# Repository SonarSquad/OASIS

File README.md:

# OASIS
Contains the complete code, circuit schematics and designs for the OASIS prototype system.
The full OASIS - A low-cost modular echosounder thesis report should also be red for a better understanding if further development of the system are to be investigated.  

**CONTENT: folder and content**
- LNA_Rev3: PCB design files for the LNA board (ALTIUM).
- Oasis_ADC_PCB: PCB design files and gerbers for the ADC board (KICAD).
- Oasis_MCU_bridge_PCB: PCB design files and gerbers for MCU board (KICAD).
- Python code and drivers: Main python script and C- code drivers for the OASIS system
- MCU_ATmega4809: Code for waveform-generation on the ATmega4809. 
- SPI_test_alternative_ADC: Example code for setting up SPI communication on the Raspberry Pi 4 (not used in OASIS prototype).  

**HARDWARE modules:**
- LNA board - Low noise amplifier. (designed and tested)
- MCU board - ATmega4809 Full-bridge module. (designed and tested)
- ADC board - ADS8422 board Analog to Digital converter. (designed and tested)
- Raspberry pi 4 model B (4GB RAM). (bought and tested)

**OASIS Prototype achievements:** 
1. System startup, Transmit a pulse at preset frequency (200kHz).
    - Pulse generaton is done on sepparate microcontroller (MCU).
    
2. Amplify returning echo with LNA.  
    
3. Sample returning echo, (switch not developed yet - two transducers used while testing, one for transmit and one for receive). 
    - Receive and sample incomming returning echo. Sampling @ 1.7 Msps.  

4. Plotting and light processing of received signal.
    - Plot: FFT. 
    - Plot: Time vs. voltage. 

________________________________________________________________________________________________________
**CONTACT:** 
- Martin Ericsson - tlf: 92649342, email: martincse94@gmail.com 
- Tor K. Gjerde - tlf: 46934462, email: torgjerde.nor@gmail.com
- Torbjørn Willson - tlf: 46810798, email: torbjorw@ntnu.no
- Einar Avdem - tlf: 98813120, email: einarav@stud.ntnu.no

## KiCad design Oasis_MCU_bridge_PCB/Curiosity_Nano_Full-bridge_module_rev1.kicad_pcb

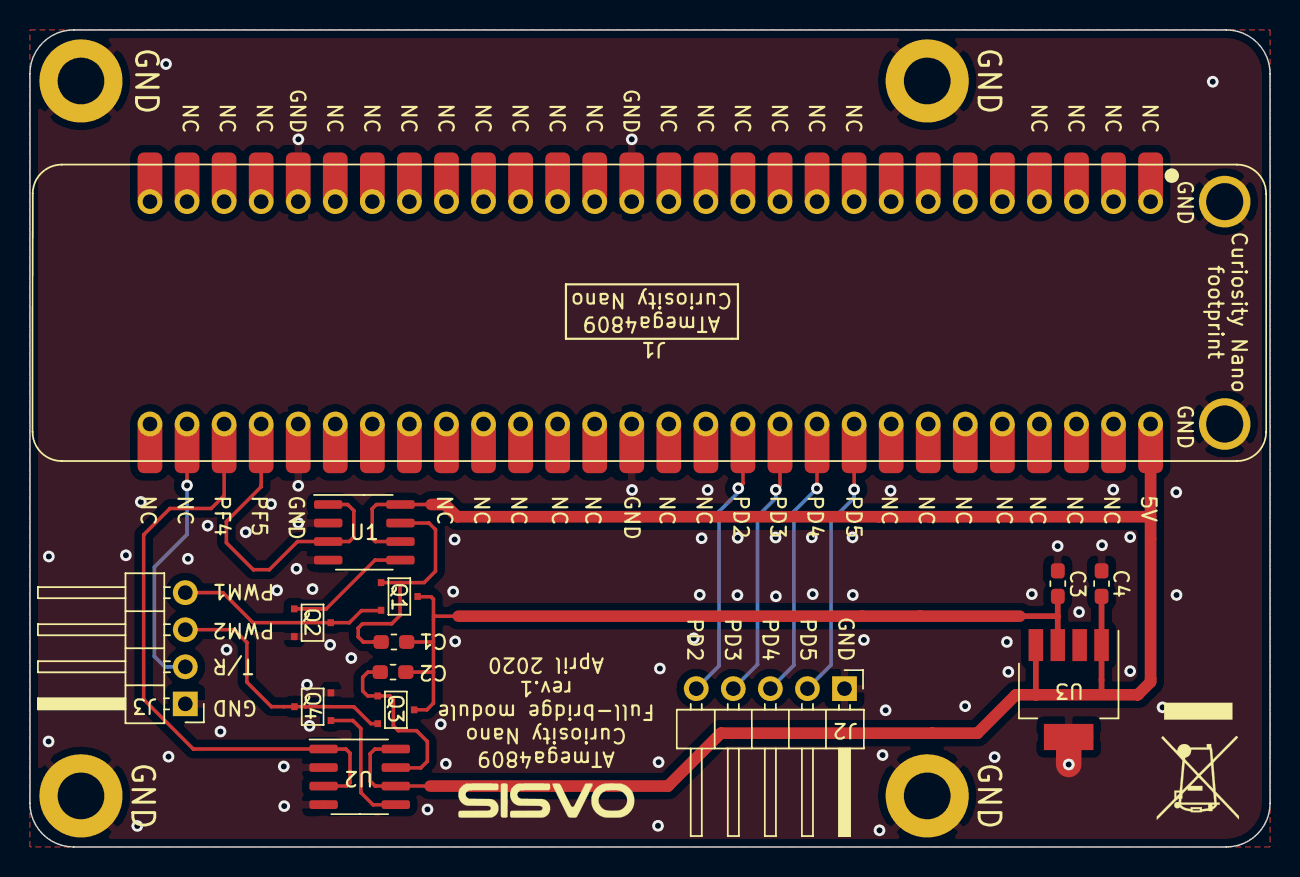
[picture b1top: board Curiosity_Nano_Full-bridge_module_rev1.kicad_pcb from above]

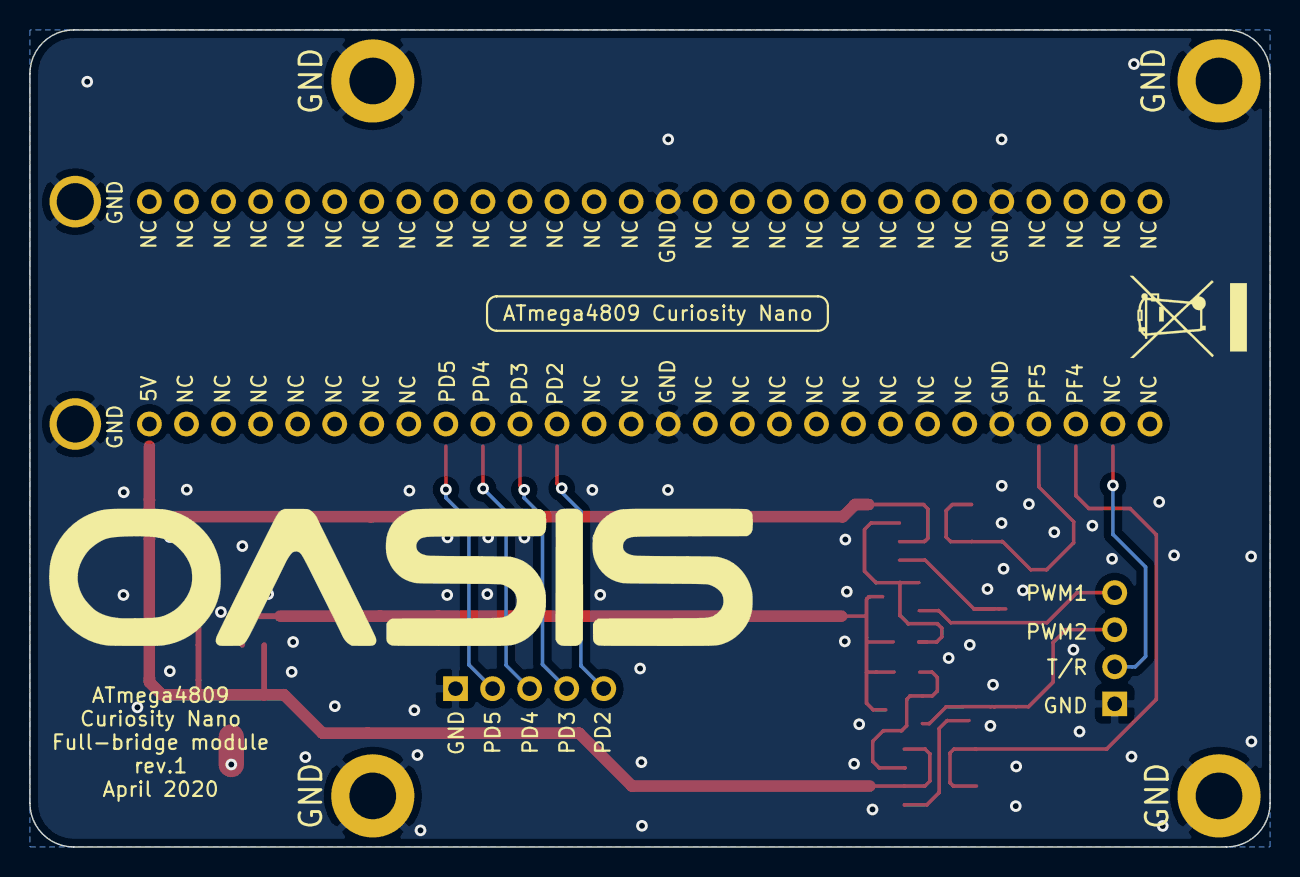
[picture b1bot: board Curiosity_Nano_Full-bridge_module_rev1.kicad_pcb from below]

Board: 2 copper layers, 85.0 x 56.0 mm, 18 parts (4 on the bottom side), 16 nets.

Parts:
C1, C2: 560pF; C_0603_1608Metric_Pad1.05x0.95mm_HandSolder
C3, C4: 1µF; C_0603_1608Metric_Pad1.05x0.95mm_HandSolder
GND: MountingHole_3.2mm_M3_ISO7380_Pad
GND#2, GND#3, GND#4: MountingHole_3.2mm_M3_ISO7380_Pad
J1: CuNanConn; ATmega4809_Curisoity_Nano
J2: Conn_01x05; PinHeader_1x05_P2.54mm_Horizontal
J3: Conn_01x04; PinHeader_1x04_P2.54mm_Horizontal
Q1, Q2, Q3, Q4: PMV164ENEA; BSS123
U1, U2: LTC1693-2; SOIC-8_3.9x4.9mm_P1.27mm
U3: LP38693MP; SOT-223-5

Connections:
+3V3: C1.1, C2.1, C3.2, Q1.3, Q3.3, U3.3
+5V: C4.1, J1.29, U1.6, U1.8, U2.6, U2.8, U3.1, U3.4
Earth: C3.1, C4.2, GND.1, GND#2.1, GND#3.1, GND#4.1, J1.15, J1.24, J1.43, J1.52, J1.57, J2.1, J3.1, Q2.2, Q4.2, U1.2, U1.4, U2.2, U2.4, U3.5
unnamed: C1.2, Q1.1, U1.7
unnamed: C2.2, Q3.1, U2.7
unnamed: Q2.1, U1.5
unnamed: Q4.1, U2.5
PD2: J1.40, J2.5
PD3: J1.39, J2.4
PD4: J1.38, J2.3
PD5: J1.37, J2.2
PWM1_IN: J1.53, U1.1, U1.3
PWM1_OUT: J3.4, Q1.2, Q2.3
PWM2_IN: J1.54, U2.1, U2.3
PWM2_OUT: J3.3, Q3.2, Q4.3
T-R: J1.55, J3.2

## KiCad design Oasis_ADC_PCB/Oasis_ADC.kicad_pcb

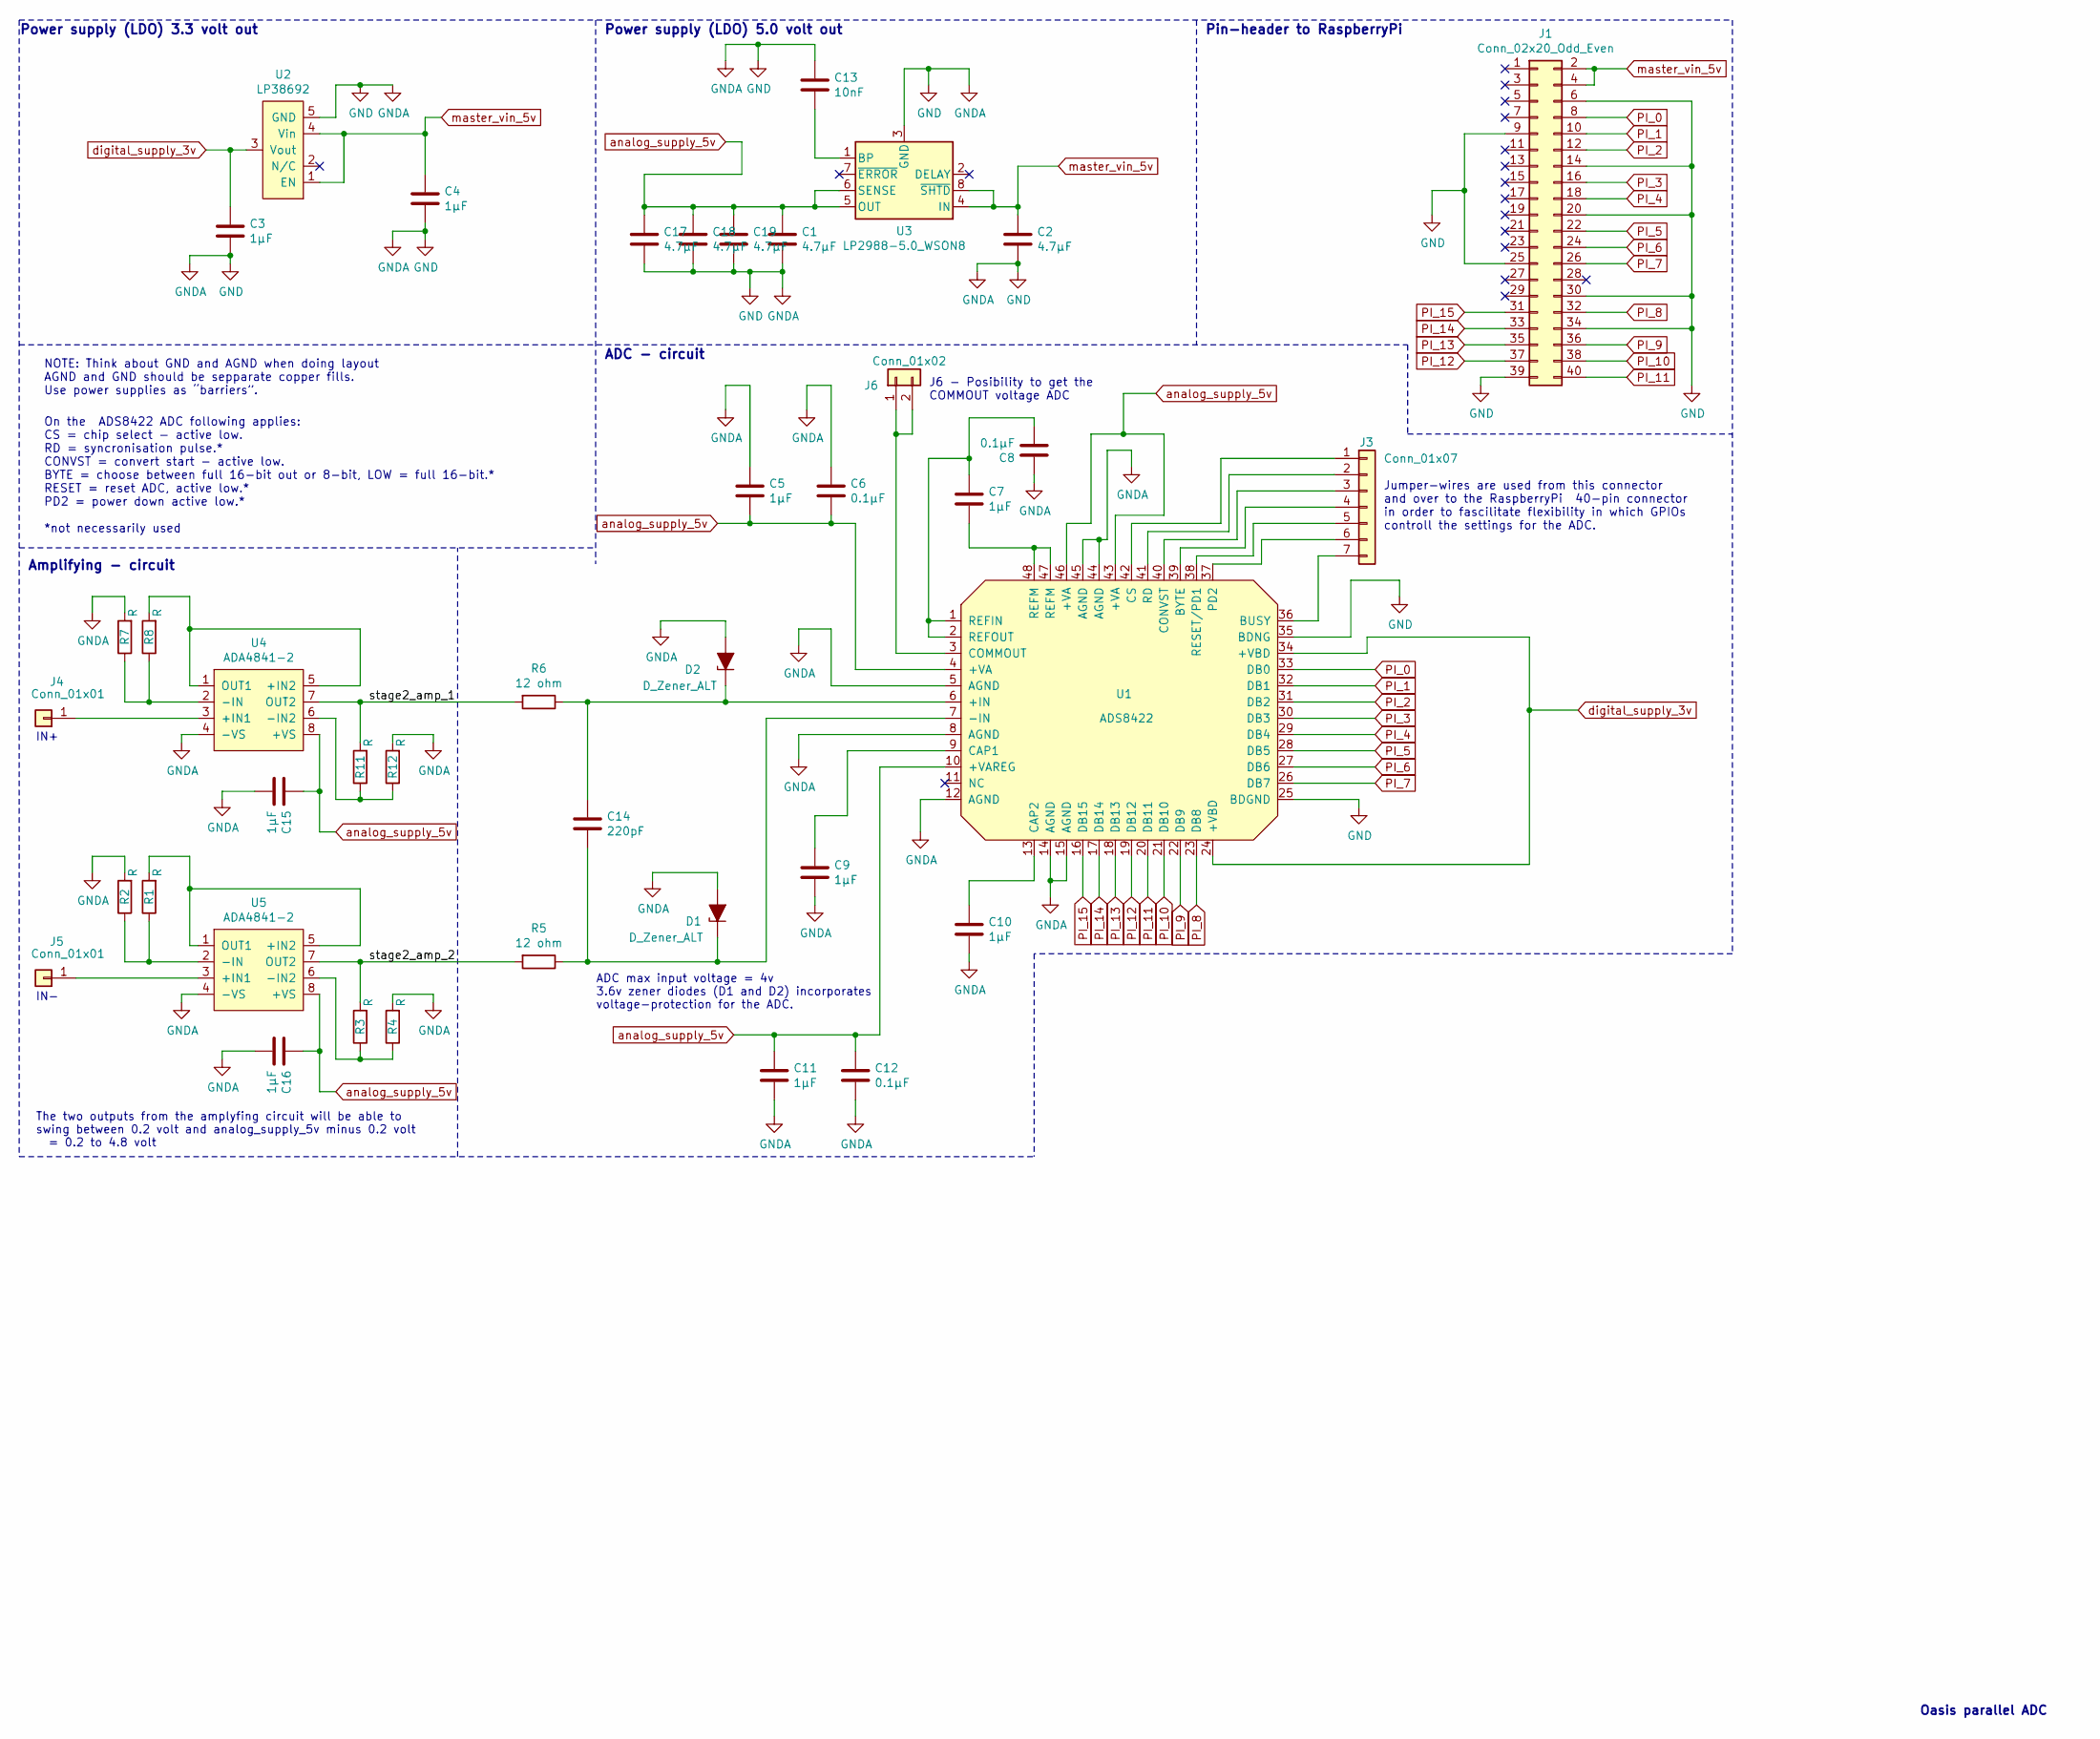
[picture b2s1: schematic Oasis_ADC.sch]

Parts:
C1, C2, C19: 4.7µF; C_0603_1608Metric_Pad1.05x0.95mm_HandSolder
C3, C4, C5, C7, C9, C10, C11, C15, C16: 1µF; C_0603_1608Metric_Pad1.05x0.95mm_HandSolder
C6, C8, C12: 0.1µF; C_0603_1608Metric_Pad1.05x0.95mm_HandSolder
C13: 10nF; C_0603_1608Metric_Pad1.05x0.95mm_HandSolder
C14: 220pF; C_0603_1608Metric_Pad1.05x0.95mm_HandSolder
C17, C18: 4.7µF; C_0805_2012Metric
D1, D2: D_Zener_ALT; D_SOD-323
J1: Conn_02x20_Odd_Even; PinHeader_2x20_P2.54mm_Vertical
J3: Conn_01x07; PinHeader_1x07_P2.54mm_Vertical
J4, J5: Conn_01x01; PinHeader_1x01_P2.54mm_Vertical
J6: Conn_01x02; PinHeader_1x02_P2.54mm_Vertical
R1, R2, R3, R4, R7, R8, R11, R12: R; R_0805_2012Metric
R5, R6: 12 ohm; R_0805_2012Metric
U1: ADS8422
U2: LP38692; SOT-223-5
U3: LP2988-5.0_WSON8; WSON-8_4x4mm_P0.8mm
U4, U5: ADA4841-2; SOIC-8_3.9x4.9mm_P1.27mm

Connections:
/stage2_amp_1: R6.2, R11.2, U4.7 (OUT2)
/stage2_amp_2: R3.2, R5.2, U5.7 (OUT2)
GND: C1.2, C2.2, C3.2, C4.2, C5.1, C6.1, C8.1, C9.2, C10.2, C11.2, C12.2, C13.1, C15.2, C16.2, C17.2, C18.2, C19.2, D1.2 (A), D2.2 (A), J1.6, J1.9, J1.14, J1.20, J1.25, J1.30, J1.34, J1.39, R2.2, R4.2, R7.2, R12.2, U1.5 (AGND), U1.8 (AGND), U1.12 (AGND), U1.14 (AGND), U1.15 (AGND), U1.25 (BDGND), U1.35 (BDNG), U1.44 (AGND), U1.45 (AGND), U2.5 (GND), U3.3 (GND), U3.9 (GND), U4.4 (-VS), U5.4 (-VS)
unnamed: C7.1, U1.47 (REFM), U1.48 (REFM)
unnamed: C7.2, C8.2, U1.1 (REFIN), U1.2 (REFOUT)
unnamed: C9.1, U1.9 (CAP1)
unnamed: C10.1, U1.13 (CAP2)
unnamed: C13.2, U3.1 (BP)
unnamed: C14.1, D2.1 (K), R6.1, U1.6 (+IN)
unnamed: C14.2, D1.1 (K), R5.1, U1.7 (-IN)
unnamed: J3.1, U1.42 (CS)
unnamed: J3.2, U1.41 (RD)
unnamed: J3.3, U1.40 (CONVST)
unnamed: J3.4, U1.39 (BYTE)
unnamed: J3.5, U1.38 (RESET/PD1)
unnamed: J3.6, U1.37 (PD2)
unnamed: J3.7, U1.36 (BUSY)
unnamed: J4.1, U4.3 (+IN1)
unnamed: J5.1, U5.3 (+IN1)
unnamed: J6.1, J6.2, U1.3 (COMMOUT)
unnamed: R1.1, R2.1, U5.2 (-IN)
unnamed: R1.2, U5.1 (OUT1), U5.5 (+IN2)
unnamed: R3.1, R4.1, U5.6 (-IN2)
unnamed: R7.1, R8.1, U4.2 (-IN)
unnamed: R8.2, U4.1 (OUT1), U4.5 (+IN2)
unnamed: R11.1, R12.1, U4.6 (-IN2)
PI_0: J1.8, U1.33 (DB0)
PI_1: J1.10, U1.32 (DB1)
PI_2: J1.12, U1.31 (DB2)
PI_3: J1.16, U1.30 (DB3)
PI_4: J1.18, U1.29 (DB4)
PI_5: J1.22, U1.28 (DB5)
PI_6: J1.24, U1.27 (DB6)
PI_7: J1.26, U1.26 (DB7)
PI_8: J1.32, U1.23 (DB8)
PI_9: J1.36, U1.22 (DB9)
PI_10: J1.38, U1.21 (DB10)
PI_11: J1.40, U1.20 (DB11)
PI_12: J1.37, U1.19 (DB12)
PI_13: J1.35, U1.18 (DB13)
PI_14: J1.33, U1.17 (DB14)
PI_15: J1.31, U1.16 (DB15)
analog_supply_5v: C1.1, C5.2, C6.2, C11.1, C12.1, C15.1, C16.1, C17.1, C18.1, C19.1, U1.4 (+VA), U1.10 (+VAREG), U1.43 (+VA), U1.46 (+VA), U3.5 (OUT), U3.6 (SENSE), U4.8 (+VS), U5.8 (+VS)
digital_supply_3v: C3.1, U1.24 (+VBD), U1.34 (+VBD), U2.3 (Vout)
master_vin_5v: C2.1, C4.1, J1.2, J1.4, U2.1 (EN), U2.4 (Vin), U3.4 (IN), U3.8 (~SHTD)

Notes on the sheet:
On the ADS8422 ADC following applies: CS = chip select - active low. RD = syncronisation pulse.* CONVST = convert start - active low. BYTE = choose between full 16-bit out or 8-bit, LOW = full 16-bit.* RESET = reset ADC, active low.* PD2 = power down active low.* *not necessarily used
NOTE: Think about GND and AGND when doing layout AGND and GND should be sepparate copper fills. Use power supplies as “barriers”.
Power supply (LDO) 3.3 volt out
Pin-header to RaspberryPi
Power supply (LDO) 5.0 volt out
Amplifying - circuit
ADC - circuit
Jumper-wires are used from this connector and over to the RaspberryPi 40-pin connector in order to fascilitate flexibility in which GPIOs controll the settings for the ADC.
J6 - Posibility to get the COMMOUT voltage ADC
Oasis parallel ADC
The two outputs from the amplyfing circuit will be able to swing between 0.2 volt and analog_supply_5v minus 0.2 volt = 0.2 to 4.8 volt
ADC max input voltage = 4v 3.6v zener diodes (D1 and D2) incorporates voltage-protection for the ADC.
IN+
IN-

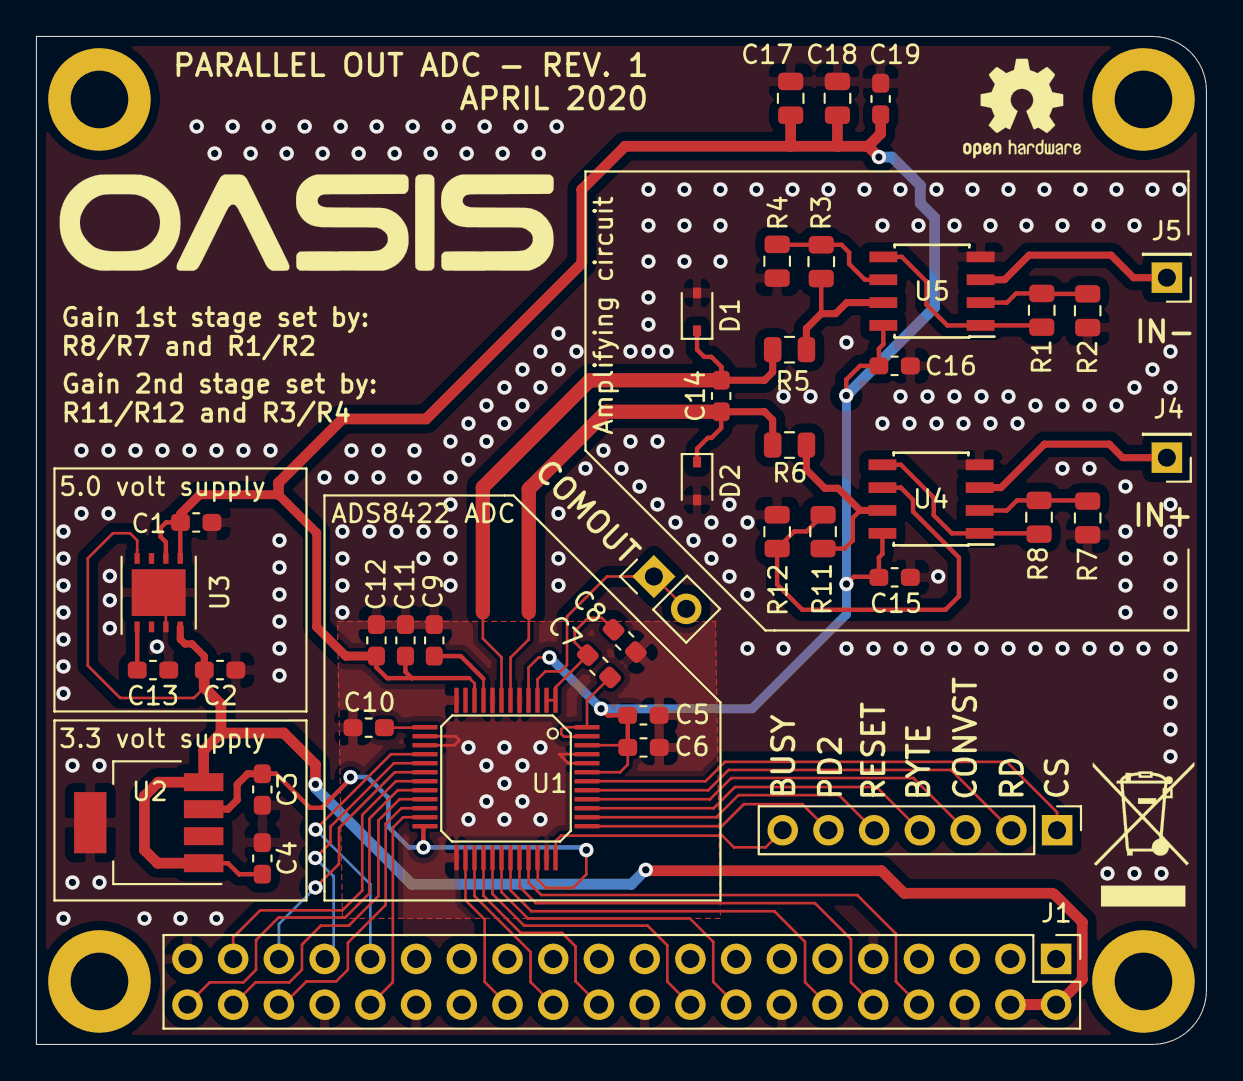
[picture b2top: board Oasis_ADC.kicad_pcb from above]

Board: 2 copper layers, 65.0 x 56.0 mm, 41 parts (0 on the bottom side), 45 nets.

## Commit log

2020-05-01 Comment
2020-05-24 LNA rev 3b files
